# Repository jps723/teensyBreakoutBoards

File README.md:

# Teensy 3.6/4 Build Notes 2/9/20

**Design Notes:**

The breakout boards each have associated proto boards in the designs.  Both boards can be milled on a single piece of FR-1 in just over 1hr if the alignment bracket on the othermill is removed.

## Build Process
Bit: 1/32”
Mill Time: ~33mins each

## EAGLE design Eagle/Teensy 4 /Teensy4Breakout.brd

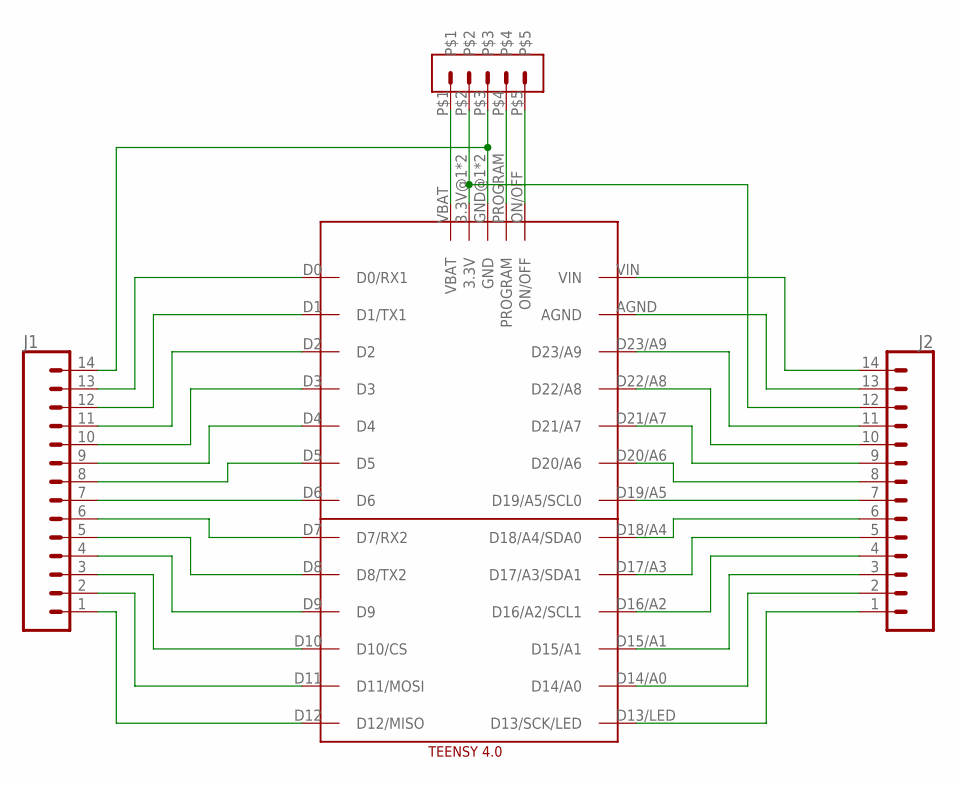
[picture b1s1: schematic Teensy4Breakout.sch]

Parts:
J1, J2: CONN_14LONGPADS; 1X14-LONGPADS
U$1: HEADER1X5
U$4: TEENSY4.0-NOPOGO

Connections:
unnamed: U$1.P$1, U$4.VBAT
unnamed: J2.12, U$1.P$2, U$4.3.3V@1 (3.3V), U$4.3.3V@2 (3.3V)
unnamed: J1.14, U$1.P$3, U$4.GND@1 (GND), U$4.GND@2 (GND)
unnamed: U$1.P$4, U$4.PROGRAM
unnamed: U$1.P$5, U$4.ON/OFF
unnamed: J1.11, U$4.D2
unnamed: J1.13, U$4.D0 (D0/RX1)
unnamed: J1.12, U$4.D1 (D1/TX1)
unnamed: J1.10, U$4.D3
unnamed: J1.9, U$4.D4
unnamed: J1.8, U$4.D5
unnamed: J1.7, U$4.D6
unnamed: J1.6, U$4.D7 (D7/RX2)
unnamed: J1.5, U$4.D8 (D8/TX2)
unnamed: J1.4, U$4.D9
unnamed: J1.3, U$4.D10 (D10/CS)
unnamed: J1.2, U$4.D11 (D11/MOSI)
unnamed: J1.1, U$4.D12 (D12/MISO)
unnamed: J2.14, U$4.VIN
unnamed: J2.13, U$4.AGND
unnamed: J2.11, U$4.D23/A9
unnamed: J2.10, U$4.D22/A8
unnamed: J2.9, U$4.D21/A7
unnamed: J2.8, U$4.D20/A6
unnamed: J2.7, U$4.D19/A5 (D19/A5/SCL0)
unnamed: J2.6, U$4.D18/A4 (D18/A4/SDA0)
unnamed: J2.5, U$4.D17/A3 (D17/A3/SDA1)
unnamed: J2.4, U$4.D16/A2 (D16/A2/SCL1)
unnamed: J2.3, U$4.D15/A1
unnamed: J2.2, U$4.D14/A0
unnamed: J2.1, U$4.D13/LED (D13/SCK/LED)

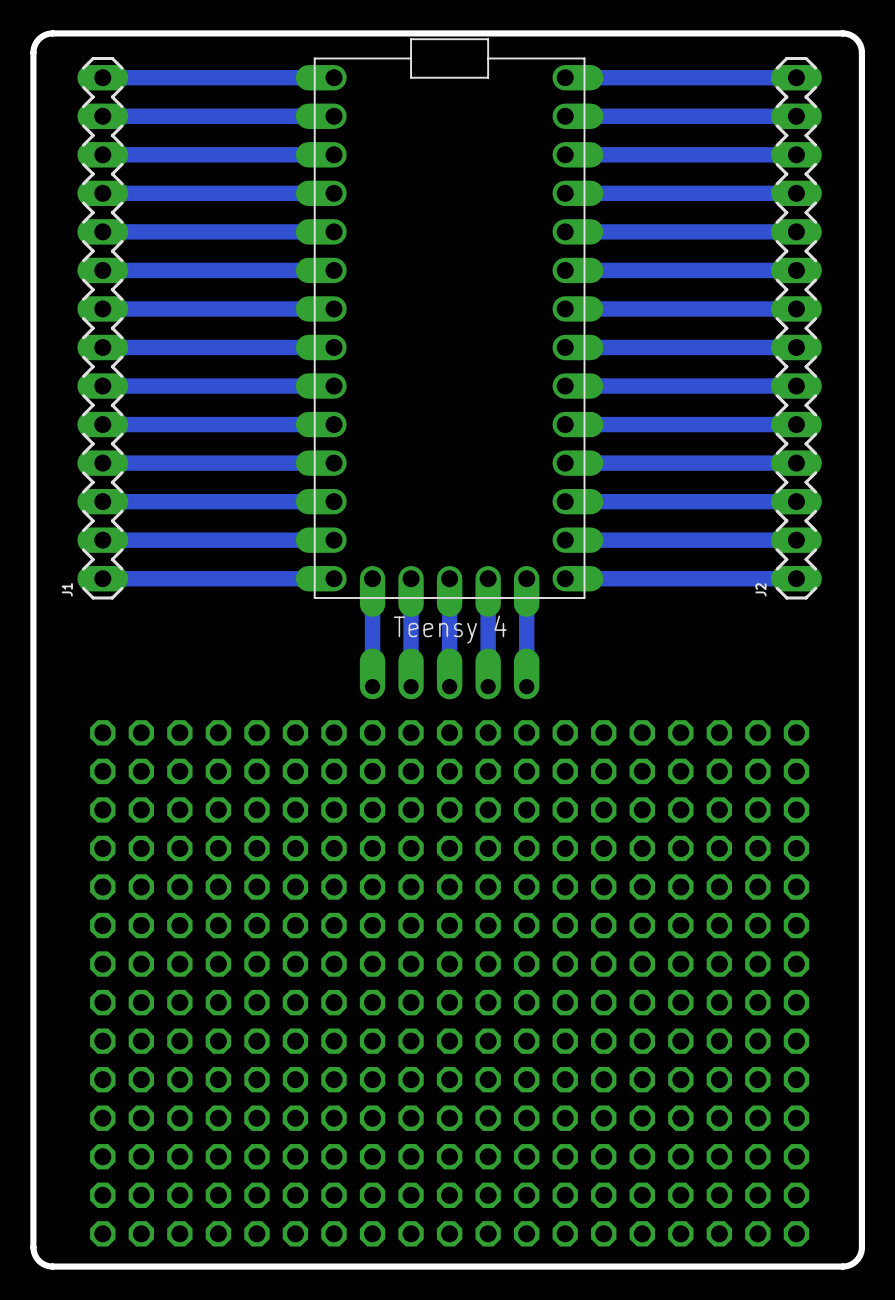
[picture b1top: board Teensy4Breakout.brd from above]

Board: 2 copper layers, 54.6 x 81.3 mm, 4 parts (0 on the bottom side), 31 nets.

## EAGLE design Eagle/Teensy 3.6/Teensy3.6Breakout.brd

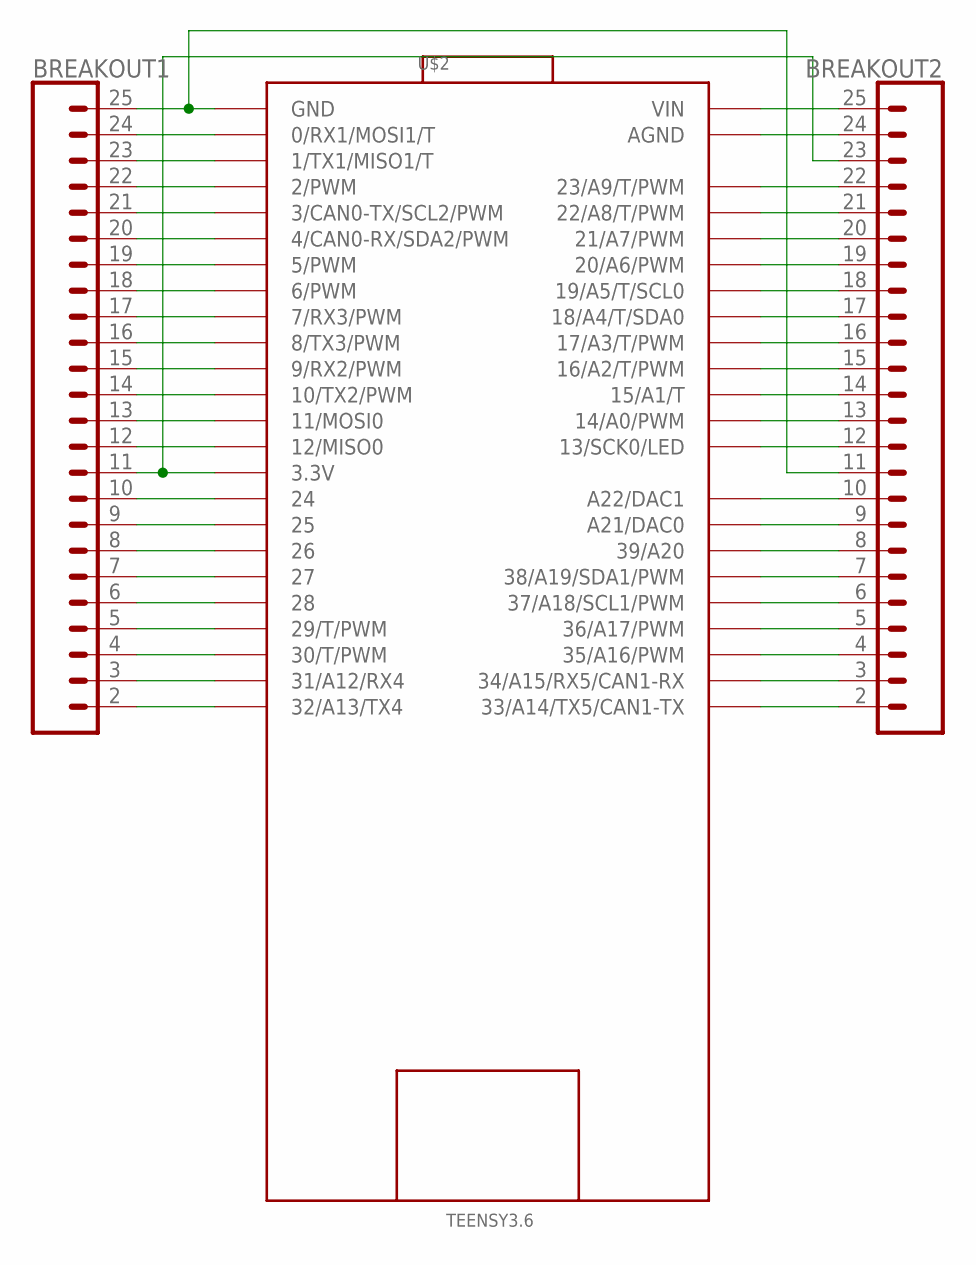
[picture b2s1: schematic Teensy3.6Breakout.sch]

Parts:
BREAKOUT1, BREAKOUT2: CONN_24LONGPADS; 1X24_LONGPADS
U$2: TEENSY3.6

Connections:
unnamed: BREAKOUT1.25, BREAKOUT2.11, U$2.GND, U$2.GND1 (GND)
unnamed: BREAKOUT1.24, U$2.0 (0/RX1/MOSI1/T)
unnamed: BREAKOUT1.23, U$2.1 (1/TX1/MISO1/T)
unnamed: BREAKOUT1.22, U$2.2 (2/PWM)
unnamed: BREAKOUT1.21, U$2.3 (3/CAN0-TX/SCL2/PWM)
unnamed: BREAKOUT1.20, U$2.4 (4/CAN0-RX/SDA2/PWM)
unnamed: BREAKOUT1.19, U$2.5 (5/PWM)
unnamed: BREAKOUT1.18, U$2.6 (6/PWM)
unnamed: BREAKOUT1.17, U$2.7 (7/RX3/PWM)
unnamed: BREAKOUT1.16, U$2.8 (8/TX3/PWM)
unnamed: BREAKOUT1.15, U$2.9 (9/RX2/PWM)
unnamed: BREAKOUT1.14, U$2.10 (10/TX2/PWM)
unnamed: BREAKOUT1.13, U$2.11 (11/MOSI0)
unnamed: BREAKOUT1.12, U$2.12 (12/MISO0)
unnamed: BREAKOUT1.11, BREAKOUT2.23, U$2.3.3V, U$2.3.3V3 (3.3V)
unnamed: BREAKOUT1.10, U$2.24
unnamed: BREAKOUT1.9, U$2.25
unnamed: BREAKOUT1.8, U$2.26
unnamed: BREAKOUT1.7, U$2.27
unnamed: BREAKOUT1.6, U$2.28
unnamed: BREAKOUT1.5, U$2.29 (29/T/PWM)
unnamed: BREAKOUT1.4, U$2.30 (30/T/PWM)
unnamed: BREAKOUT1.3, U$2.31/A12 (31/A12/RX4)
unnamed: BREAKOUT1.2, U$2.32/A13 (32/A13/TX4)
unnamed: BREAKOUT2.8, U$2.39/A20
unnamed: BREAKOUT2.7, U$2.38/A19 (38/A19/SDA1/PWM)
unnamed: BREAKOUT2.6, U$2.37/A18 (37/A18/SCL1/PWM)
unnamed: BREAKOUT2.5, U$2.36/A17 (36/A17/PWM)
unnamed: BREAKOUT2.4, U$2.35/A16 (35/A16/PWM)
unnamed: BREAKOUT2.3, U$2.34/A15 (34/A15/RX5/CAN1-RX)
unnamed: BREAKOUT2.2, U$2.33/A14 (33/A14/TX5/CAN1-TX)
unnamed: BREAKOUT2.9, U$2.A21 (A21/DAC0)
unnamed: BREAKOUT2.10, U$2.A22 (A22/DAC1)
unnamed: BREAKOUT2.12, U$2.13 (13/SCK0/LED)
unnamed: BREAKOUT2.13, U$2.14/A0 (14/A0/PWM)
unnamed: BREAKOUT2.14, U$2.15/A1 (15/A1/T)
unnamed: BREAKOUT2.15, U$2.16/A2 (16/A2/T/PWM)
unnamed: BREAKOUT2.16, U$2.17/A3 (17/A3/T/PWM)
unnamed: BREAKOUT2.17, U$2.18/A4 (18/A4/T/SDA0)
unnamed: BREAKOUT2.18, U$2.19/A5 (19/A5/T/SCL0)
unnamed: BREAKOUT2.19, U$2.20/A6 (20/A6/PWM)
unnamed: BREAKOUT2.20, U$2.21/A7 (21/A7/PWM)
unnamed: BREAKOUT2.21, U$2.22/A8 (22/A8/T/PWM)
unnamed: BREAKOUT2.22, U$2.23/A9 (23/A9/T/PWM)
unnamed: BREAKOUT2.24, U$2.AGND
unnamed: BREAKOUT2.25, U$2.P$1 (VIN), U$2.VIN

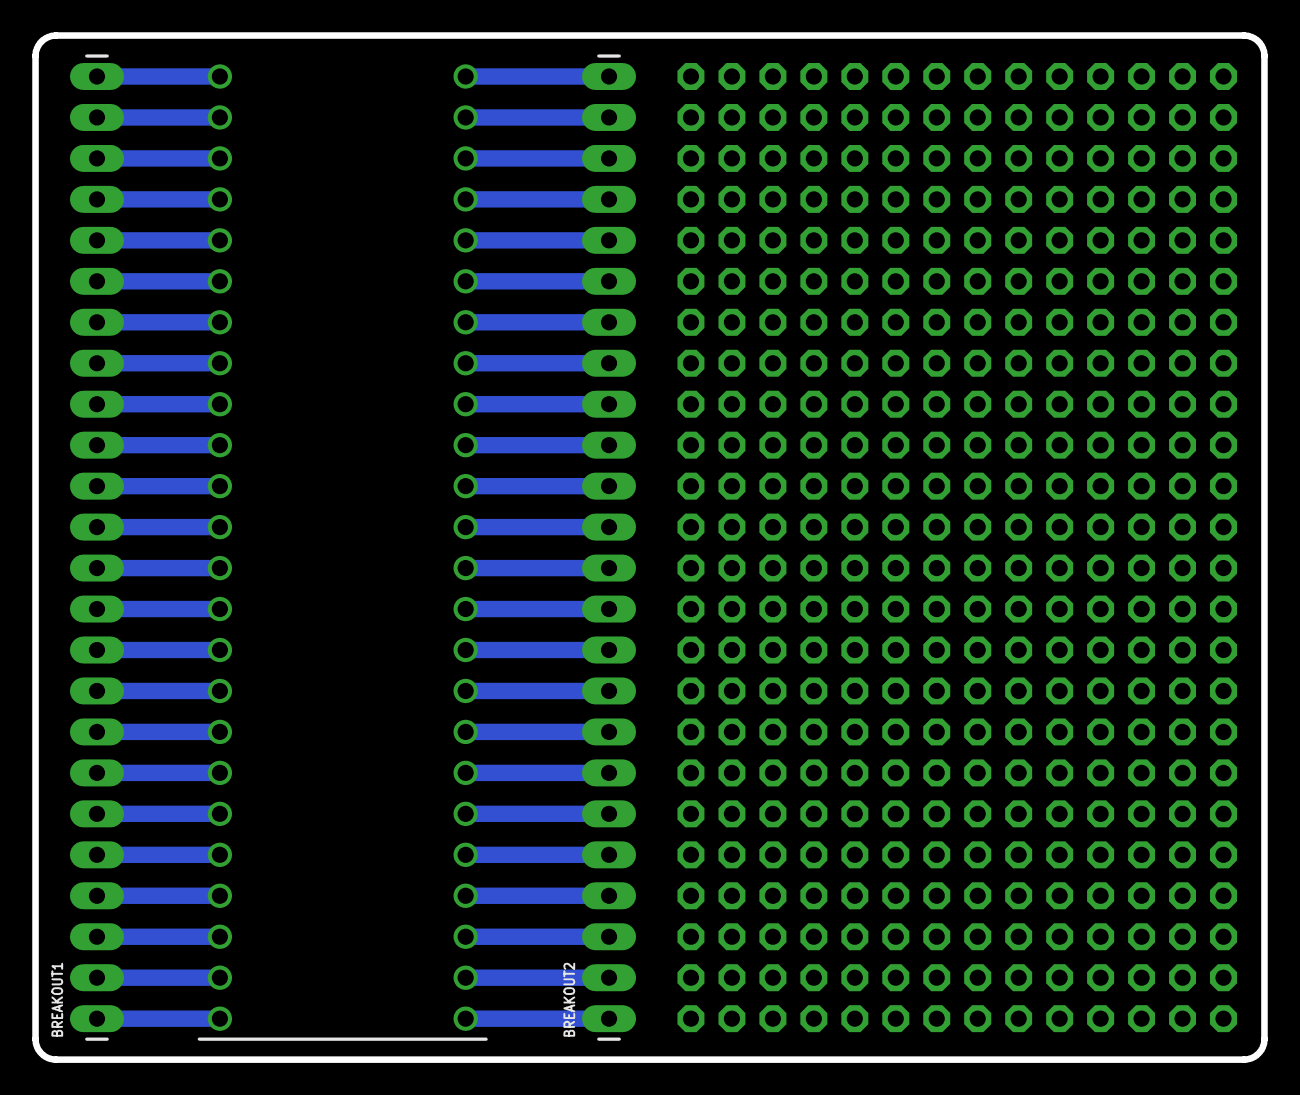
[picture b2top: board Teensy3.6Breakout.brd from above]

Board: 2 copper layers, 76.2 x 63.5 mm, 3 parts (0 on the bottom side), 46 nets.

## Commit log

2020-10-29 Added image

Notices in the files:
parts and their libraries:
SparkFun-Connectors: Licensing: Creative Commons ShareAlike 4.0 International - https://creativecommons.org/licenses/by-sa/4.0
